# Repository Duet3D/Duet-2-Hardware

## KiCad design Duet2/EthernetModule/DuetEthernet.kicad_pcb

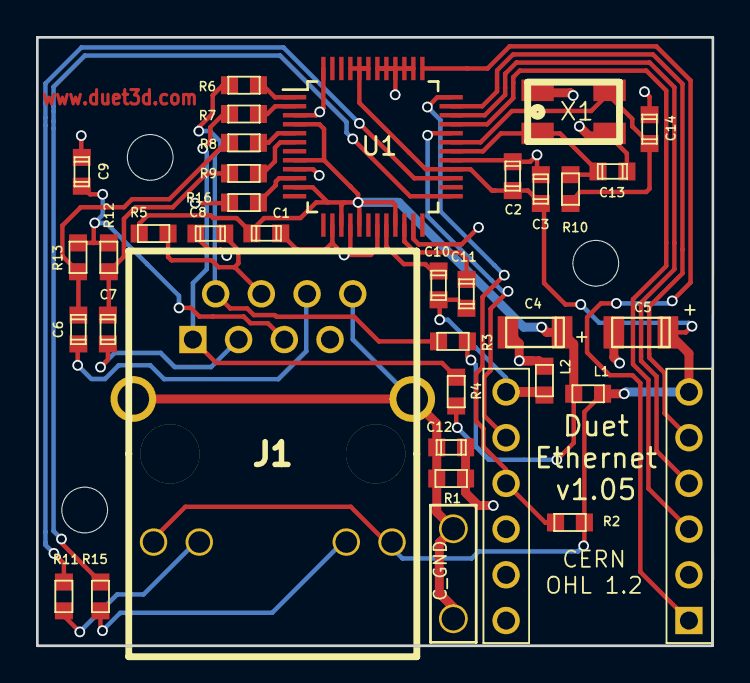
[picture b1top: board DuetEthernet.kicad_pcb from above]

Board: 2 copper layers, 37.5 x 33.8 mm, 36 parts (0 on the bottom side), 32 nets.

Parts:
C1, C2, C3: 0u1; C_0603
C4, C5: 10uF/16V; C_1206_pol
C6, C7: 6n8; C_0603
C8: 22n; C_0603
C9, C11: 10n; C_0603
C10: 4u7; C_0603
C12: 0u01 +200V; C_0603
C13, C14: 18p; C_0603
J1: RJ45+MAG
J2: CONN_ALT_HEADER; CONN_ALT_HEADER_th
J3: C_GND; 2.8mm_Spade_terminal
L1, L2: L_MINI; R_0603
R1, R10: 1M; R_0603
R2: 4K7; R_0603
R3, R4, R12, R13: 49R9; R_0603
R5: 10R; R_0603
R6, R7, R8, R9: 33R; R_0603
R11, R15: 220R; R_0603
R16: 12K4; R_0603
U1: W5500; LQFP-48_7x7mm_Pitch0.5mm
X1: CRYSTAL_4PIN; Xtal_5x3.2

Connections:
+3V3: C2.1, C3.1, C5.1, J1.9, J1.12, J2.6, L1.2, R2.2, U1.28, U1.43, U1.44, U1.45
+3V3_A: C1.1, C4.1, L1.1, R3.2, R4.2, R5.2, U1.4, U1.8, U1.11, U1.15, U1.17, U1.21
ACTLED: R11.2, U1.27
AGND: C1.2, C4.2, C8.2, C9.2, L2.1, R16.1, U1.3, U1.9, U1.14, U1.16, U1.19, U1.48
GND: C2.2, C3.2, C5.2, C10.2, C11.2, C12.1, C13.2, C14.2, J2.10, J2.15, L2.2, R1.1, U1.23, U1.29, U1.38, U1.39, U1.40, U1.41, U1.42, X1.2, X1.4
INTn: J2.12, R2.1, U1.36
LINKLED: R15.2, U1.25
MISO: J2.4, U1.34
MOSI: J2.5, U1.35
unnamed: C6.1, R8.1, R13.2
unnamed: C6.2, J1.6
unnamed: C7.1, R9.1, R12.2
unnamed: C7.2, J1.3
unnamed: C8.1, J1.4, R5.1
unnamed: C9.1, J1.5, R12.1, R13.1
unnamed: C10.1, U1.20
unnamed: C11.1, U1.22
unnamed: C12.2, J1.8, J1.13, J1.14, J3.1, R1.2
unnamed: C13.1, R10.2, U1.30, X1.1
unnamed: C14.1, R10.1, U1.31, X1.3
unnamed: J1.1, R4.1, R7.1
unnamed: J1.2, R3.1, R6.1
unnamed: J1.10, R11.1
unnamed: J1.11, R15.1
unnamed: R6.2, U1.1
unnamed: R7.2, U1.2
unnamed: R8.2, U1.5
unnamed: R9.2, U1.6
unnamed: R16.2, U1.10
RSTn: J2.1, U1.37
SCLK: J2.3, U1.33
SCSn: J2.11, U1.32

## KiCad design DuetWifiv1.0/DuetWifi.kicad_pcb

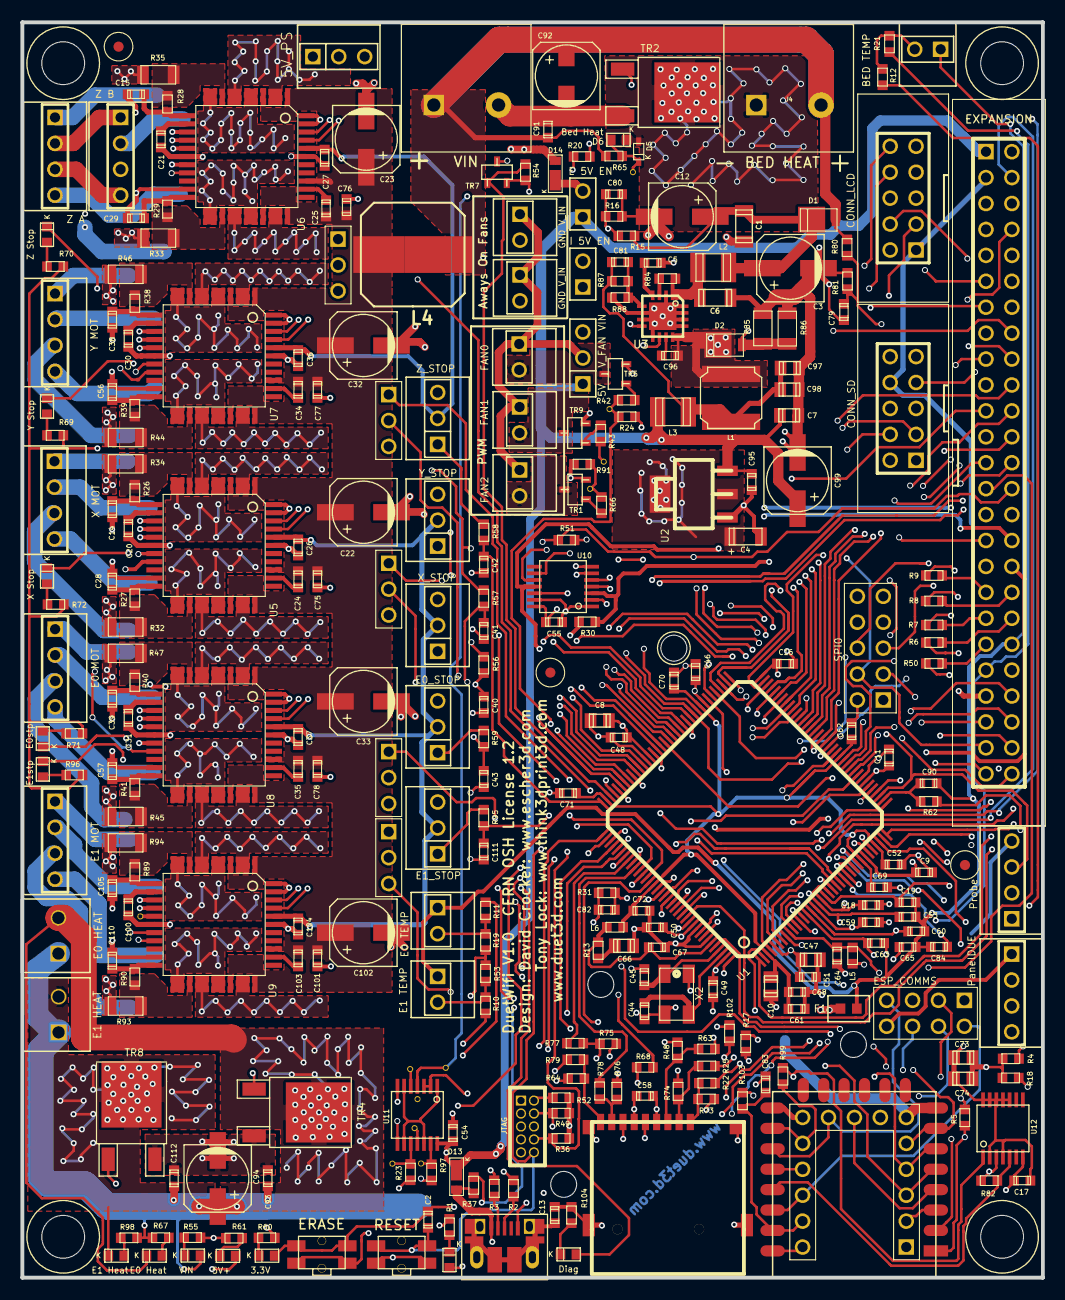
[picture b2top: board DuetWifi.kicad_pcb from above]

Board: 4 copper layers, 100.0 x 123.0 mm, 311 parts (1 on the bottom side), 262 nets.

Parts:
C1, C6: 10u 35V; C_1206
C2, C13, C79, C80, C81, C90: 0u01; C_0603
C3, C12, C22, C23, C32, C33, C102: 100u 35V; C_ELEC_6.3x7.7
C4: 10u TANT; C_1206_pol
C5, C9, C11, C16, C17, C26, C27, C36, C37, C40, C41, C42, C43, C46, C48, C49, C50, C51, C52, C54, C55, C61, C62, C64, C67, C69, C70, C71, C72, C82, C91, C93, C104, C111, C112: 0u1; C_0603
C7, C8, C10, C47, C73, C74, C97, C98: 10u; C_0805
C14, C15, C28, C29, C38, C39, C56, C57, C105, C110: 0u01 X7R 10% 50V; C_0603
C18, C19, C53, C58, C59, C60, C63, C65, C68, C84: 2u2; C_0603
C20, C21, C30, C31, C100: 0u47; C_0603
C24, C25, C34, C35, C103: 0u1 50V; C_0603
C44, C45: 10p; C_0603
C66: 4u7; C_0805
C75, C76, C77, C78, C101: 1u 50V; C_0603
C83: DNP 47p; C_0603
C92, C94, C99: 100u; C_ELEC_6.3x7.7
C95: DNP 1u; C_0603
C96: 22nF; C_0603
D1, D2: SS3P4; DO-220AA
D3: USB; D_0603
D4: Diag; D_0603
D5: SOD-523F
D6: Bed Heat; D_0603
D7: E0 Heat; D_0603
D9: Y Stop; D_0603
D10: Z Stop; D_0603
D11: E0stp; D_0603
D12: X Stop; D_0603
D13, D14: SS14M; uSMA
D15: VIN; D_0603
D16: 3.3V; D_0603
D17: 5V+; D_0603
D19: E1stp; D_0603
D20: E1 Heat; D_0603
F1: 0.25A VFA; FUSE_0603
J1: EXPANSION; PIN_ARRAY_25X2
J2: FAN2; PIN_ARRAY_2X1
J3: 5V V_FAN VIN; CONN_3x1
J4: BED HEAT; TERM_2-WAY_6.35mm
J5: BED TEMP; PIN_ARRAY_2X1
J6: E1 MOT; PIN_ARRAY_4x1
J7: Z B; PIN_ARRAY_4x1
J8: Y MOT; PIN_ARRAY_4x1
J9: X MOT; PIN_ARRAY_4x1
J10: E0 MOT; PIN_ARRAY_4x1
J11: E0 HEAT; 3.5MM_2X1
J12: E0 TEMP; PIN_ARRAY_2X1
J13: E1 HEAT; 3.5MM_2X1
J14: E1 TEMP; PIN_ARRAY_2X1
J15: uSDHC; uSD_SKT
J16: CONN_ALT_HEADER
J19: Z_STOP; PIN_ARRAY_3X1
J20: 5V_PS; PIN_ARRAY_3X1
J21: JTAG; MICRO_5x2
J22: USB; uUSB_new
J23: VIN; TERM_2-WAY_6.35mm
J24, J31: GND V_IN; PIN_ARRAY_2X1
J25: FAN0; PIN_ARRAY_2X1
J28: Probe; PIN_ARRAY_4x1
J29: FAN1; PIN_ARRAY_2X1
J30: PanelDUE; PIN_ARRAY_4x1
J32: Y_STOP; PIN_ARRAY_3X1
J33: X_STOP; PIN_ARRAY_3X1
J34: E0_STOP; PIN_ARRAY_3X1
J35: E1_STOP; PIN_ARRAY_3X1
J36: Z A; PIN_ARRAY_4x1
J37: SPI0; MAX_TEMP_DB
J39: ESP_COMMS; CONN_4x2
JP9: I 5V EN; JUMPER
JP10: E 5V EN; JUMPER
L1: 10uH; L_6x6
L2, L3: 1uH; C_1210
L4: DNP 4.7uH Approx 10A; TPC-XL-Bridged
L5, L6: 10uH 100Mhz; R_0603
M1, M2, M3: FID; Fiducial_1mm_Dia_2.54mm_Outer_CopperTop
M4, M5, M6, M7: MOUNTING; Fixing_M4
M8: LOGO
P1: CONN_SD; IDC_PIN_ARRAY_5x2
P2: CONN_LCD; IDC_PIN_ARRAY_5x2
R1, R4, R17, R61, R99, R102, R104: 2K2; R_0603
R2, R3: 27R 1%; R_0603
R5: 470R; R_0603
R6, R7, R8, R9, R10, R11, R12, R24, R50, R51, R62, R63, R64, R91: 10K; R_0603
R13: 1R; R_0603
R15, R80: 47K 1%; R_0603
R16, R19, R21, R53, R81: 4K7 1%; R_0603
R18, R54, R55, R65, R67, R98: 4K7; R_0603
R20, R23, R97: 180R; R_0603
R22, R25, R48, R60, R77, R78, R79: 220R; R_0603
R26, R27, R28, R29, R38, R39, R40, R41, R89, R90: 22R; R_0603
R30: 68R; R_0603
R31: 47K; R_0603
R32, R33, R34, R35, R44, R45, R46, R47, R93, R94: 0R051; R_1206
R36, R49, R52: DNP 100K; R_0603
R37: 27K; R_0603
R42, R43, R56, R57, R58, R59, R66, R69, R70, R71, R72, R95, R96: 1K; R_0603
R68: 100R; R_0603
R73, R74, R75, R76: DNP 47K; R_0603
R82: 0R DNP; R_0603
R84: 100K; R_0603
R85, R86: 0R1; R_1206
R87: 3K92; R_0603
R88: 750R; R_0603
R103: 1K0; R_0603
S1: RESET; SW_SIDE_1_lugs
S2: ERASE; SW_SIDE_1_lugs
TP1, TP5: Z_Stp_Tp; CONN_3x1
TP2: Y_Stp_Tp; CONN_3x1
TP3: X_Stp_Tp; CONN_3x1
TP4: E0_Stp_Tp; CONN_3x1
TP6, TP7, TP8, TP9, TP10, TP11, TP12, TP13, TP14, TP15, TP16: TP; TP_via
TR1, TR5, TR7, TR9: PMV40UN2; SOT-23
TR2, TR4, TR8: IPD036N04L; D-PAK
U1: ATSAM4E8E; LQFP144
U2: TC2117-3.3VDBTR; SOT-223
U3: A4403; QFN16-4x4
U4: ESP-07/12; ESP-12E
U5, U6, U7, U8, U9: TMC2660
U10: 74HC125; TSSOP-14
U11: 74HCT02; TSSOP-14
U12: 74HC74; TSSOP-14
X2: CRYSTAL_4PIN; Xtal_5x3.2

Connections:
5V_IN: D14.1, J20.1
+3.3V: C2.1, C4.1, C8.1, C9.1, C11.1, C16.1, C17.1, C26.1, C27.1, C36.1, C37.1, C46.1, C47.1, C48.1, C49.1, C50.1, C51.1, C55.1, C58.1, C73.1, C74.1, C104.1, D16.1, J1.3, J1.43, J15.4, J16.6, J19.2, J21.1, J28.4, J32.2, J33.2, J34.2, J35.2, J37.8, L5.2, P1.8, P2.1, R36.1, R49.1, R51.1, R52.1, R63.2, R64.2, R69.2, R70.2, R71.2, R72.2, R73.2, R74.2, R75.2, R76.2, R96.2, S2.3, S2.4, U1.5, U1.30, U1.43, U1.72, U1.80, U1.96, U1.134, U1.143, U2.2, U2.4, U4.8, U5.40, U6.40, U7.40, U8.40, U9.40, U10.14, U11.2, U11.3, U12.2, U12.4, U12.10, U12.11, U12.12, U12.13, U12.14
+5V: C7.1, C54.1, C95.1, C99.1, D13.2, D17.1, J1.1, J3.1, J30.1, J39.8, JP10.1, L3.1, U2.3, U11.14
/Processor/VDDCORE: C10.1, C52.1, C61.1, C62.1, C68.1, C69.1, C70.1, C71.1, C72.1, L6.1, U1.3, U1.29, U1.33, U1.50, U1.81, U1.107, U1.123
ADC: J16.7, J39.4, U4.2
ADVREF: C64.1, J1.41, L5.1, R19.2, R21.2, R53.2, U1.9
BED-: D5.2, D6.2, J4.1, TR2.D
BED_PWM: R20.2, TP9.1, U11.4
CS3: J37.7, U1.117
CS4: J37.9, U1.120
CS5: J1.50, U1.56
D6_TestPoint: D5.1, D6.1, R65.1, TP16.1
DDM: R3.2, U1.136
DDP: R2.2, U1.137
E0-: D7.2, J11.2, TR4.D
E0_DIR: TP4.2, U1.99, U8.41
E0_EN: TP4.3, U1.103, U8.18
E0_MOT_1A: J10.2, U8.5.6, U8.10.1
E0_MOT_1B: J10.1, U8.2.3, U8.7.8
E0_MOT_2A: J10.3, U8.26.7, U8.31.2
E0_MOT_2B: J10.4, U8.23.4, U8.28.9
E0_PWM: R23.2, TP10.1, U11.10
E0_STEP: TP4.1, U1.125, U8.42
E0_STOP: C43.1, R59.1, U1.101
E0_STOP_CONN: D11.2, J34.1, R59.2
E1-: D20.2, J13.2, TR8.D
E1_DIR: TP5.2, U1.110, U9.41
E1_EN: TP5.3, U1.133, U9.18
E1_MOT_1A: J6.2, U9.5.6, U9.10.1
E1_MOT_1B: J6.1, U9.2.3, U9.7.8
E1_MOT_2A: J6.3, U9.26.7, U9.31.2
E1_MOT_2B: J6.4, U9.23.4, U9.28.9
E1_PWM: R97.2, TP11.1, U11.13
E1_STEP: TP5.1, U1.126, U9.42
E1_STOP: C111.1, R95.1, U1.100
E1_STOP_CONN: D19.2, J35.1, R95.2
E2_DIR: J1.6, U1.71
E2_EN: J1.7, U1.57
E2_STEP: J1.5, U1.131
E2_STOP: J1.4, U1.4
E3_DIR: J1.11, U1.60
E3_EN: J1.12, U1.55
E3_STEP: J1.10, U1.132
E3_STOP: J1.9, U1.6
E4_DIR: J1.16, U1.78
E4_EN: J1.17, U1.52
E4_STEP: J1.15, U1.1
E4_STOP: J1.14, U1.7
E5_DIR: J1.21, U1.74
E5_EN: J1.22, U1.53
E5_STEP: J1.20, U1.128
E5_STOP: J1.19, U1.10
E6_DIR: J1.26, U1.11
E6_EN: J1.27, U1.140
E6_STEP: J1.25, U1.47
E6_STOP: J1.24, U1.25
EDR_CONN: J16.12, R17.1, U4.18
ENC_A: P2.4, U1.36
ENC_B: P2.3, U1.48
ENC_SW: P1.7, U1.35
ENN: J1.28, R51.2, U1.54, U5.19, U6.19, U7.19, U8.19, U9.19
ERASE: S2.1, S2.2, U1.87
ESP_DATA_RDY: R17.2, U1.2
ESP_EN: J16.2, R18.1, U1.28, U4.3
ESP_RST: J16.1, R5.2, U1.27
FAN0: R24.2, R42.2, TP12.1, U1.127
FAN0-: J25.2, TR5.D
FAN1: R43.2, TP13.1, U1.13
FAN1-: J29.2, TR9.D
FAN2: R66.2, R91.2, TP14.1, U1.102
FAN2-: J2.2, TR1.D
GND: C1.2, C3.2, C4.2, C5.2, C6.2, C7.2, C8.2, C9.2, C10.2, C11.2, C12.2, C13.2, C14.2, C15.2, C16.2, C17.2, C20.2, C21.2, C22.2, C23.2, C26.2, C27.2, C28.2, C29.2, C30.2, C31.2, C32.2, C33.2, C36.2, C37.2, C38.2, C39.2, C40.2, C41.2, C42.2, C43.2, C44.2, C45.2, C46.2, C47.2, C48.2, C49.2, C50.2, C51.2, C52.2, C54.2, C55.2, C56.2, C57.2, C58.2, C61.2, C62.2, C64.2, C66.2, C67.2, C68.2, C69.2, C70.2, C71.2, C72.2, C73.2, C74.2, C75.2, C76.2, C77.2, C78.2, C79.2, C80.2, C82.2, C83.2, C91.2, C92.2, C93.2, C94.2, C95.2, C97.2, C98.2, C99.2, C100.2, C101.2, C102.2, C104.2, C105.2, C110.2, C111.2, C112.2, F1.2, J1.2, J1.30, J1.42, J15.6, J15.G, J16.10, J19.3, J20.3, J21.3, J21.5, J21.9, J22.5, J23.2, J24.2, J28.2, J30.2, J31.2, J32.3, J33.3, J34.3, J35.3, J37.2, J39.1, JP9.1, P1.2, P2.2, R1.2, R4.2, R16.2, R18.2, R24.1, R31.2, R32.1, R33.1, R34.1, R35.1, R44.1, R45.1, R46.1, R47.1, R54.2, R55.2, R60.2, R61.2, R81.2, R85.1, R86.1, R88.2, R91.1, R93.1, R94.1, R104.1, S1.1, S1.2, TR1.S, TR2.S, TR4.S, TR5.S, TR7.S, TR8.S, TR9.S, U1.8, U1.44, U1.61, U1.85, U1.95, U1.104, U1.115, U1.135, U1.138, U2.1, U3.2, U3.6, U3.7, U3.9, U3.13, U3.14, U3.15, U3.16, U3.17, U4.15, U5.17, U5.21, U5.39, U5.43, U5.44, U6.17, U6.21, U6.39, U6.43, U6.44, U7.17, U7.21, U7.39, U7.43, U7.44, U8.17, U8.21, U8.39, U8.43, U8.44, U9.17, U9.21, U9.39, U9.43, U9.44, U10.1, U10.4, U10.7, U10.9, U10.10, U10.13, U11.7, U12.7, X2.2, X2.4
GPIO2: J16.9, J39.7, U4.17
GPIO5: J16.13, J39.2, U4.20
GPIO16: J16.8, J39.6, U4.4
HEATER0: TP6.1, U1.23, U11.5
HEATER1: TP7.1, U1.22, U11.8
HEATER2: TP8.1, U1.45, U11.11
HEATER3: J1.8, U1.40
HEATER4: J1.13, U1.58
HEATER5: J1.18, U1.82
HEATER6: J1.23, U1.94
HEATER7: J1.31, U1.49
LCD_DB4: P2.10, U1.63
LCD_DB5: P2.9, U1.65
LCD_DB6: P2.7, U1.67
LCD_DB7: P2.5, U1.69
LCD_E: P2.8, U1.59
LCD_RS: P2.6, U1.76
MCCDA: R48.2, U1.112
MCCK: R68.2, U1.129
MCDA0: R77.2, U1.116
MCDA1: R78.2, U1.118
MCDA2: R22.2, U1.62
MCDA3: R25.2, U1.70
MISO: J16.4, U1.68, U4.6
MOSI: J16.5, U1.42, U4.7
NPCS0: R99.2, U1.64, U12.1
NPCS0_CONN: J16.11, R99.1, U4.16
unnamed: C1.1, C3.1, C12.1, D1.2, L2.2, R15.1
unnamed: C5.1, U3.4
unnamed: C6.1, L2.1, R84.1, U3.1
unnamed: C13.1, J22.CE
unnamed: C14.1, R26.2, U5.12
unnamed: C15.1, R28.2, U6.12
unnamed: C18.1, R11.2, U1.18
unnamed: C19.1, R12.2, U1.19
unnamed: C20.1, U5.13
unnamed: C21.1, U6.13
unnamed: C24.2, U5.35
unnamed: C25.2, U6.35
unnamed: C28.1, R27.2, U5.22
unnamed: C29.1, R29.2, U6.22
unnamed: C30.1, U7.13
unnamed: C31.1, U8.13
unnamed: C34.2, U7.35
unnamed: C35.2, U8.35
unnamed: C38.1, R38.2, U7.12
unnamed: C39.1, R40.2, U8.12
unnamed: C44.1, U1.142, X2.3
unnamed: C45.1, U1.141, X2.1
unnamed: C53.1, R10.2, U1.17
unnamed: C56.1, R39.2, U7.22
unnamed: C57.1, R41.2, U8.22
unnamed: C59.1, R9.2, U1.16
unnamed: C60.1, R8.2, U1.15
unnamed: C63.1, R7.2, U1.14
unnamed: C65.1, R6.2, U1.12
unnamed: C66.1, R13.2
unnamed: C67.1, L6.2, R13.1, U1.139
unnamed: C81.1, C97.1, C98.1, L1.1, L3.2, R87.1
unnamed: C81.2, R87.2, R88.1, U3.5
unnamed: C84.1, R50.2, U1.24
unnamed: C90.1, R62.2, U1.38
unnamed: C96.1, U3.11
unnamed: C96.2, D2.2, L1.2, U3.12
unnamed: C100.1, U9.13
unnamed: C103.2, U9.35
unnamed: C105.1, R89.2, U9.12
unnamed: C110.1, R90.2, U9.22
unnamed: D2.1, R85.2, R86.2, U3.8
unnamed: D3.2, R1.1
unnamed: D4.2, R104.2
unnamed: D7.1, R67.1
unnamed: D9.1, R69.1
unnamed: D10.1, R70.1
unnamed: D11.1, R71.1
unnamed: D12.1, R72.1
unnamed: D14.2, JP10.2
unnamed: D15.2, R55.1
unnamed: D16.2, R60.1
unnamed: D17.2, R61.1
unnamed: D19.1, R96.1
unnamed: D20.1, R98.1
unnamed: J15.1, R22.1, R73.1
unnamed: J15.2, R25.1, R74.1
unnamed: J15.3, R48.1, R63.1
unnamed: J15.5, R68.1
unnamed: J15.7, R75.1, R77.1
unnamed: J15.8, R76.1, R78.1
unnamed: J15.9, R64.1, R79.1
unnamed: J22.2, R3.1
unnamed: J22.3, R2.1
unnamed: J7.1, J36.2
unnamed: J7.4, J36.3
unnamed: JP9.2, U3.10
unnamed: R4.1, R5.1, U4.1
unnamed: R20.1, TR2.G
unnamed: R23.1, TR4.G
unnamed: R26.1, R34.2, U5.9
unnamed: R27.1, R32.2, U5.25
unnamed: R28.1, R35.2, U6.9
unnamed: R29.1, R33.2, U6.25
unnamed: R38.1, R46.2, U7.9
unnamed: R39.1, R44.2, U7.25
unnamed: R40.1, R47.2, U8.9
unnamed: R41.1, R45.2, U8.25
unnamed: R42.1, TR5.G
unnamed: R43.1, TR9.G
unnamed: R66.1, TR1.G
unnamed: R82.2, U4.19, U12.5
unnamed: R84.2, U3.3
unnamed: R89.1, R94.2, U9.9
unnamed: R90.1, R93.2, U9.25
unnamed: R97.1, TR8.G
unnamed: U11.1, U11.6, U11.9, U11.12
PB4/TDI: J21.8, R36.2, U1.105
PB5/TDO: J21.6, U1.109
PB6/TMS: J1.29, J21.2, R52.2, U1.79
PB7/TCK: J21.4, R49.2, U1.89
PS_ON: R54.1, TR7.G, U1.106
PS_ON_IN: J20.2, TR7.D
PWR_FAIL_DET1: C80.1, R15.2, R16.1, U1.31
PWR_FAIL_DET2: C79.1, R80.2, R81.1, U1.41
RESET: C2.2, J1.44, J21.10, S1.3, S1.4, U1.83
SAM_TFR_RDY: R82.1, U1.34, U12.3
SD_CD: R79.2, U1.122
SPCK: J16.3, U1.51, U4.5
SPI0_CS0: P1.3, U1.130
SPI0_CS1: J37.3, U1.26
SPI0_CS2: J37.1, U1.111
SPI0_MISO: J1.49, J37.6, P1.6, U1.21
SPI0_MOSI: J1.48, J37.5, P1.5, U1.20
SPI0_SCK: J1.47, J37.4, P1.4, U1.144
SPI1_MISO: J1.34, U1.32, U5.14, U6.14, U7.14, U8.14, U9.14
SPI1_MOSI: U1.37, U10.12
SPI1_MOSI_BUFF: J1.33, U5.15, U6.15, U7.15, U8.15, U9.15, U10.11
SPI1_SCK: U1.46, U10.2
SPI1_SCK_BUFF: R30.1, TP15.1, U5.16, U6.16, U7.16, U8.16, U9.16
SPI1_SCK_BUFF_EXP: J1.32, R30.2, U10.3
STEPPER_V_IN: C22.1, C23.1, C24.1, C25.1, C32.1, C33.1, C34.1, C35.1, C75.1, C76.1, C77.1, C78.1, C101.1, C102.1, C103.1, L4.2, U5.1, U5.4, U5.30, U5.33, U5.36, U6.1, U6.4, U6.30, U6.33, U6.36, U7.1, U7.4, U7.30, U7.33, U7.36, U8.1, U8.4, U8.30, U8.33, U8.36, U9.1, U9.4, U9.30, U9.33, U9.36
THERMISTOR0: J5.2, R12.1, R21.1
THERMISTOR1: J12.2, R11.1, R19.1
THERMISTOR2: J14.2, R10.1, R53.1
THERMISTOR3: J1.35, R9.1
THERMISTOR4: J1.36, R8.1
THERMISTOR5: J1.37, R7.1
THERMISTOR6: J1.38, R6.1
THERMISTOR7: J1.39, R50.1
TWCK0: J1.46, U1.77
TWD0: J1.45, U1.91
URXD0: J30.3, U1.75
URXD1: R102.2, U1.73
URXD1_CONN: J16.15, J39.3, R102.1, U4.22
USB_PWR_MON: C82.1, R31.1, R37.2, U1.124
UTXD0: J30.4, U1.66
UTXD1: R103.2, U1.114
UTXD1_CONN: C83.1, J16.14, J39.5, R103.1, U4.21
VBUS: D3.1, D13.1, J22.1, R37.1
VSSA: C18.2, C19.2, C53.2, C59.2, C60.2, C63.2, C65.2, C84.2, C90.2, F1.1, J1.40, J5.1, J12.1, J14.1
V_FAN: J2.1, J3.2, J24.1, J25.1, J29.1, J31.1
V_IN: C91.1, C92.1, C93.1, C94.1, C112.1, D1.1, D15.1, J3.3, J4.2, J11.1, J13.1, J23.1, L4.1, R65.2, R67.2, R80.1, R98.2
X_DIR: TP3.2, U1.98, U5.41
X_EN: TP3.3, U1.84, U5.18
X_MOT_1A: J9.2, U5.5.6, U5.10.1
X_MOT_1B: J9.1, U5.2.3, U5.7.8
X_MOT_2A: J9.3, U5.26.7, U5.31.2
X_MOT_2B: J9.4, U5.23.4, U5.28.9
X_STEP: TP3.1, U1.121, U5.42
X_STOP: C40.1, R56.1, U1.97
X_STOP_CONN: D12.2, J33.1, R56.2
Y_DIR: TP2.2, U1.92, U7.41
Y_EN: TP2.3, U1.86, U7.18
Y_MOT_1A: J8.2, U7.5.6, U7.10.1
Y_MOT_1B: J8.1, U7.2.3, U7.7.8
Y_MOT_2A: J8.3, U7.26.7, U7.31.2
Y_MOT_2B: J8.4, U7.23.4, U7.28.9
Y_STEP: TP2.1, U1.119, U7.42
Y_STOP: C41.1, R57.1, U1.93
Y_STOP_CONN: D9.2, J32.1, R57.2
Z_DIR: TP1.2, U1.88, U6.41
Z_EN: TP1.3, U1.90, U6.18
Z_MOT_1A: J7.2, U6.5.6, U6.10.1
Z_MOT_1B: J36.1, U6.2.3, U6.7.8
Z_MOT_2A: J7.3, U6.26.7, U6.31.2
Z_MOT_2B: J36.4, U6.23.4, U6.28.9
Z_PROBE_IN: J28.1, R62.1
Z_PROBE_MOD: J28.3, U1.39, U10.5
Z_PROBE_MOD_BUFF: D4.1, U10.6
Z_STEP: TP1.1, U1.113, U6.42
Z_STOP: C42.1, R58.1, U1.108
Z_STOP_CONN: D10.2, J19.1, R58.2
